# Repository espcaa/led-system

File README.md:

# Leds are fun!

Created this project in 4h to drive a very long led strip i got at (scrapyard)[https://scrapyard.hackclub.com]. I didn't have any psu or mosfets to drive it, so I created this pcb.

## Features

- has cool art
- has shiny mosfets
- has an esp32-f to control your leds wirelessly
- maybe works
- made by me

## BOM

| Name  | Qty | Total Price  |
| ------------- | ------------- | ------------- |
| PSU  | 1 | 20$ |
| JLCPCB | 1 | 60$ |

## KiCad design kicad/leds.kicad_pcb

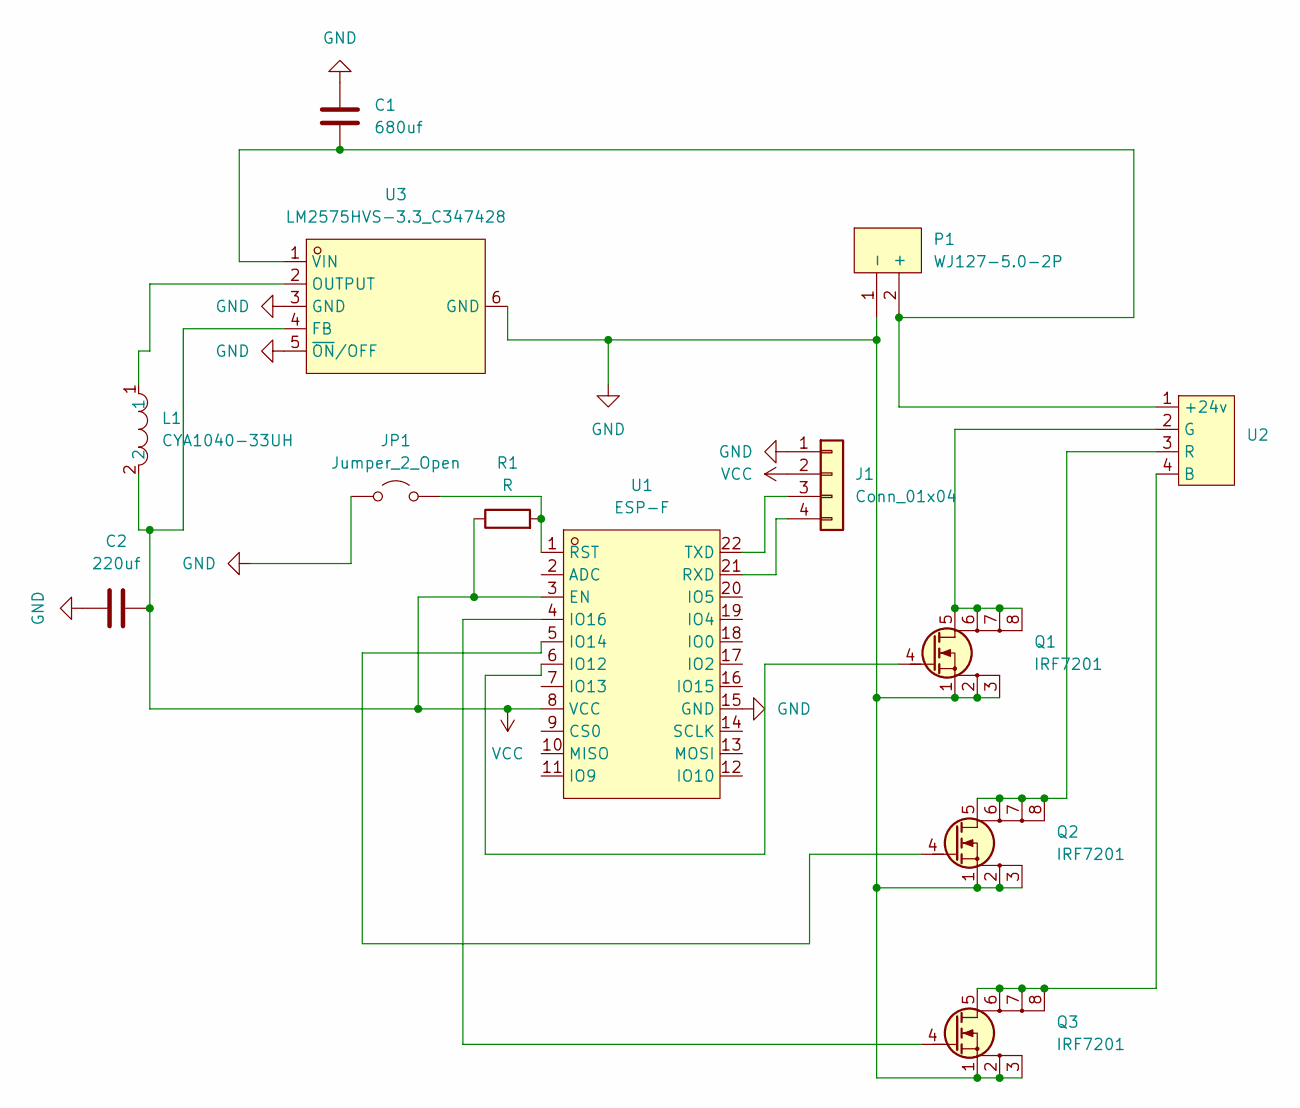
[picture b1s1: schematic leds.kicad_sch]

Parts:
C1: 680uf; CAP-SMD_BD6.3-L6.6-W6.6-FD
C2: 220uf; CAP-SMD_BD6.3-L6.6-W6.6-FD
J1: Conn_01x04; PinHeader_1x04_P2.54mm_Vertical
JP1: Jumper_2_Open; SolderJumper-2_P1.3mm_Open_Pad1.0x1.5mm
L1: CYA1040-33UH; IND-SMD_L11.6-W10.1; LCSC Part C6364680
P1: WJ127-5.0-2P; CONN-TH_2P-P5.00_CPC3703CTR; LCSC Part C3703
Q1, Q2, Q3: IRF7201; SO-8_3.9x4.9mm_P1.27mm
R1: R; R_0603_1608Metric
U1: ESP-F; WIFIM-SMD_ESP-F; LCSC Part C19949062
U2: ledstrip
U3: LM2575HVS-3.3_C347428; TO-263-5_L10.0-W8.4-P1.70-LS15.3-BR; LCSC Part C347428

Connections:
GND: C1.2, C2.2, J1.1, JP1.1 (A), P1.1 (-), Q1.1 (S), Q1.2 (S), Q1.3 (S), Q2.1 (S), Q2.2 (S), Q2.3 (S), Q3.1 (S), Q3.2 (S), Q3.3 (S), U1.15 (GND), U3.3 (GND), U3.5 (~ON/OFF), U3.6 (GND)
unnamed: J1.3, U1.22 (TXD)
unnamed: J1.4, U1.21 (RXD)
unnamed: JP1.2 (B), R1.2, U1.1 (RST)
unnamed: C1.1, P1.2 (+), U2.1 (+24v), U3.1 (VIN)
unnamed: Q1.4 (G), U1.6 (IO12)
unnamed: Q2.4 (G), U1.5 (IO14)
unnamed: Q3.4 (G), U1.4 (IO16)
unnamed: Q3.5 (D), Q3.6 (D), Q3.7 (D), Q3.8 (D), U2.4 (B)
unnamed: Q1.5 (D), Q1.6 (D), Q1.7 (D), Q1.8 (D), U2.2 (G)
unnamed: Q2.5 (D), Q2.6 (D), Q2.7 (D), Q2.8 (D), U2.3 (R)
unnamed: L1.1, U3.2 (OUTPUT)
VCC: C2.1, J1.2, L1.2, R1.1, U1.3 (EN), U1.8 (VCC), U3.4 (FB)

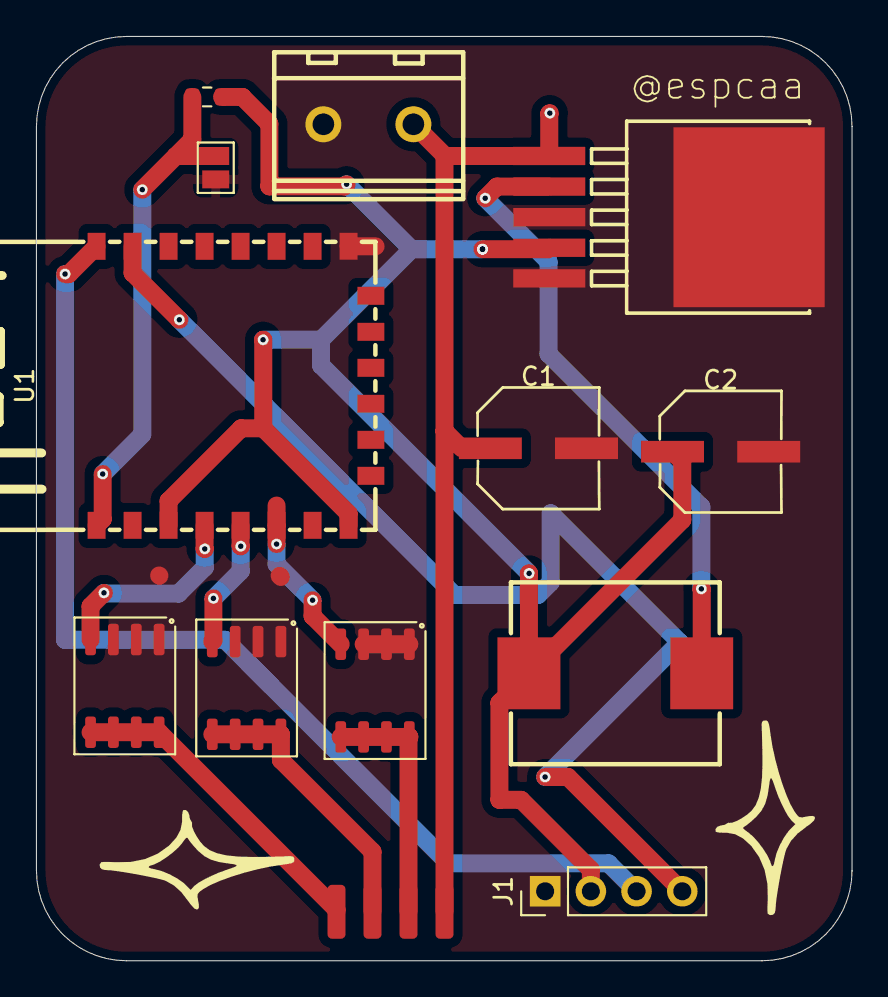
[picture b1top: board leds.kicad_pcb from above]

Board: 2 copper layers, 45.3 x 51.3 mm, 13 parts (0 on the bottom side), 13 nets.

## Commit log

2025-06-15 hiii
2025-06-15 haiii
2025-06-15 mosfets Please enter the commit message for your changes. Lines starting
2025-06-15 added the sources
2025-06-15 added the bom
2025-06-15 fixed the readmee
2025-06-15 readme or not
2025-06-15 capacitors are now smd
2025-06-15 updated bom
2025-06-15 changed the pcb file to add headers
2025-06-15 changed the silkscreen :3c
